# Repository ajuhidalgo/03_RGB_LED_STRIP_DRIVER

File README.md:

## Controlador de Tiras LED RGB con ESP32-C6-MINI

### Descripción
Este proyecto se centra en la creación de un controlador para tiras de LEDs RGB utilizando el microcontrolador **ESP32-C6-MINI**. El dispositivo está diseñado para ser compatible con **Google Home** y se conecta a través de **Wi-Fi**. El controlador permite seleccionar colores y efectos para las tiras LED.

### Componentes del Proyecto
1. **Circuito y PCB**: Diseñé el circuito y el PCB para el controlador utilizando **KiCad**. Puedes encontrar los esquemas y archivos Gerber en este repositorio.
2. **Carcasa**: Creé una carcasa en 3D para proteger el controlador con el programa **Fusion 360**. Los archivos STL y los detalles de impresión están disponibles en la carpeta de mecánica.
3. **Firmware**: El código fuente del firmware se encuentra en el repositorio. En la memoria del proyecto puedes obtener información acerca de la configuración.

### Características Clave
- **Microcontrolador**: Utilizamos el módulo **ESP32-C6-MINI** de Espressif Systems y transistores **mosfet** para controlar las tiras LED.
- **Interfaz de uso**: El dispositivo se controla a través del entorno **Google Home**. Permite la integración con la domótica del hogar, programar horarios de encendido o programar escenas. Esto lo conseguimos gracias al uso de la plataforma Sinric Pro.
- **Selección de Colores**: Los usuarios pueden elegir entre una amplia gama de colores para personalizar las tiras LED.

### Repositorio en GitHub
Puedes encontrar el código fuente, los esquemas, los archivos de Gerber, los archivos STL y más en este repositorio.

¡Buena suerte con tu proyecto! Si tienes alguna pregunta o necesitas más detalles, puedes ponerte en contacto conmigo.

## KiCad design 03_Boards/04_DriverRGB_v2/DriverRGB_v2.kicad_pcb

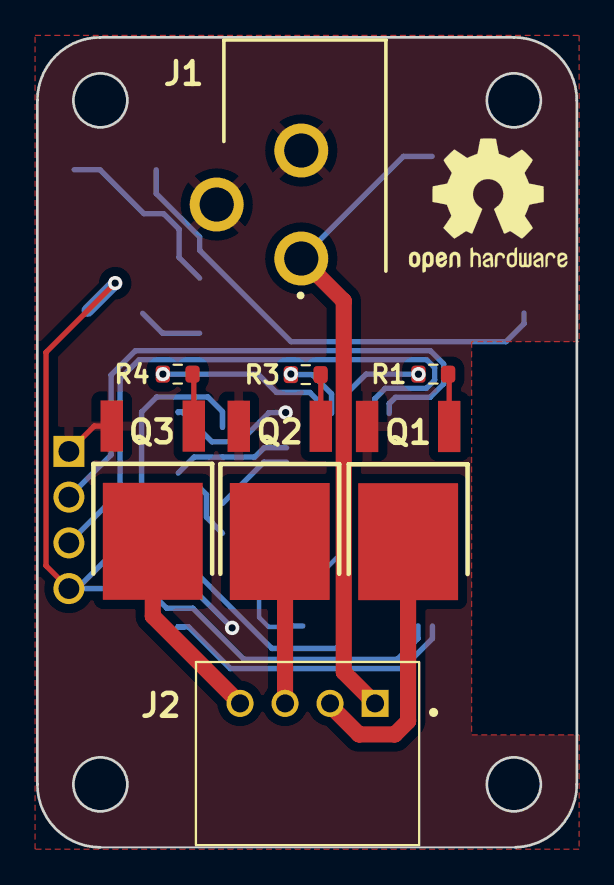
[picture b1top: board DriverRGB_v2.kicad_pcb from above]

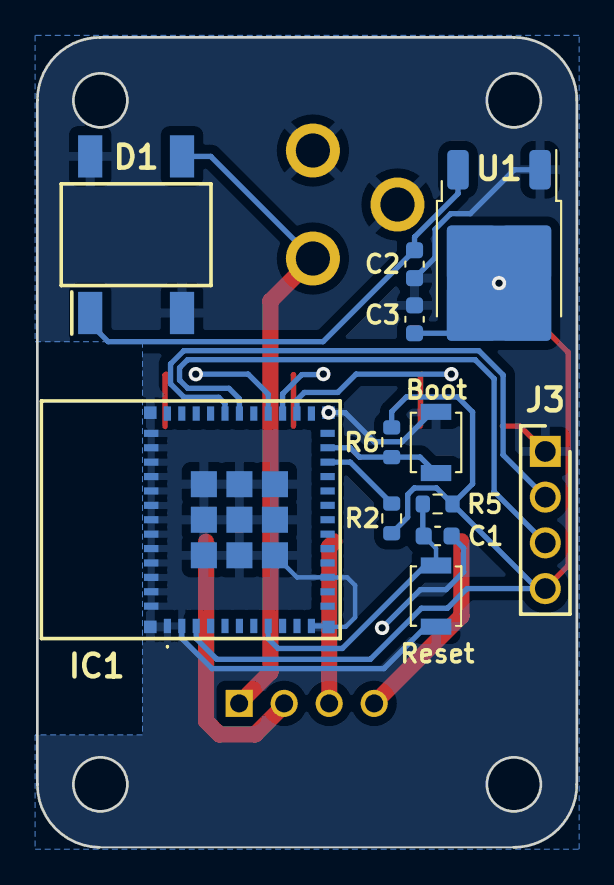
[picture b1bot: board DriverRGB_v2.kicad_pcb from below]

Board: 2 copper layers, 30.0 x 45.0 mm, 20 parts (12 on the bottom side), 18 nets.

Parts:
C1: 100nF; C_0603_1608Metric
C2, C3: 1uF; C_0603_1608Metric
D1: DF04S-E3; DF04S-E3_77
IC1: ESP32-C6-MINI-1-N4
J1: PJ-102A; PJ-102AH
J2: S4B-XH-A_LF__SN_
J3: 61300411121
Q1, Q2, Q3: FDD8880
R1, R2, R3, R4, R5, R6: 10kOhm; R_0603_1608Metric
S1: Reset; SW_SPST_B3U-1000P
S2: Boot; SW_SPST_B3U-1000P
U1: AMS1117CD-3.3; TO-252-2

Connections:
BLUE_OUT-: J2.4, Q3.3 (D)
EN: C1.1, IC1.8 (EN), R5.2, S1.2
GND: C1.2, C2.2, C3.2, D1.2 (-), D1.4, IC1.1 (GND_1), IC1.2 (GND_2), IC1.11 (GND_3), IC1.14 (GND_4), IC1.36 (GND_5), IC1.37 (GND_6), IC1.38 (GND_7), IC1.39 (GND_8), IC1.40 (GND_9), IC1.41 (GND_10), IC1.42 (GND_11), IC1.43 (GND_12), IC1.44 (GND_13), IC1.45 (GND_14), IC1.46 (GND_15), IC1.47 (GND_16), IC1.48 (GND_17), IC1.49 (GND_18), IC1.50 (GND_19), IC1.51 (GND_20), IC1.52 (GND_21), IC1.53 (GND_22), IC1.54 (GND_23), IC1.55 (GND_24), IC1.56 (GND_25), IC1.57 (GND_26), IC1.58 (GND_27), IC1.59 (GND_28), IC1.60 (GND_29), IC1.61 (GND_30), J1.2, J1.3, J3.1, Q1.2 (S), Q2.2 (S), Q3.2 (S), S1.1, S2.1, U1.1 (GND)
GREEN_OUT-: J2.3, Q2.3 (D)
IO9: IC1.23 (IO9), R6.2, S2.2
unnamed: C2.1, D1.1 (+), U1.3 (VI)
unnamed: IC1.22 (IO8), R2.2
unnamed: Q1.1 (G), R1.2
unnamed: Q2.1 (G), R3.2
unnamed: Q3.1 (G), R4.2
PWM_BLUE: IC1.26 (IO20), R4.1
PWM_GREEN: IC1.27 (IO21), R3.1
PWM_RED: IC1.28 (IO22), R1.1
PWR_IN: D1.3, J1.1, J2.1
RED_OUT-: J2.2, Q1.3 (D)
RX: IC1.30 (RXD0), J3.3
TX: IC1.31 (TXD0), J3.2
VDD: C3.1, IC1.3 (3V3), J3.4, R2.1, R5.1, R6.1, U1.2 (VO)

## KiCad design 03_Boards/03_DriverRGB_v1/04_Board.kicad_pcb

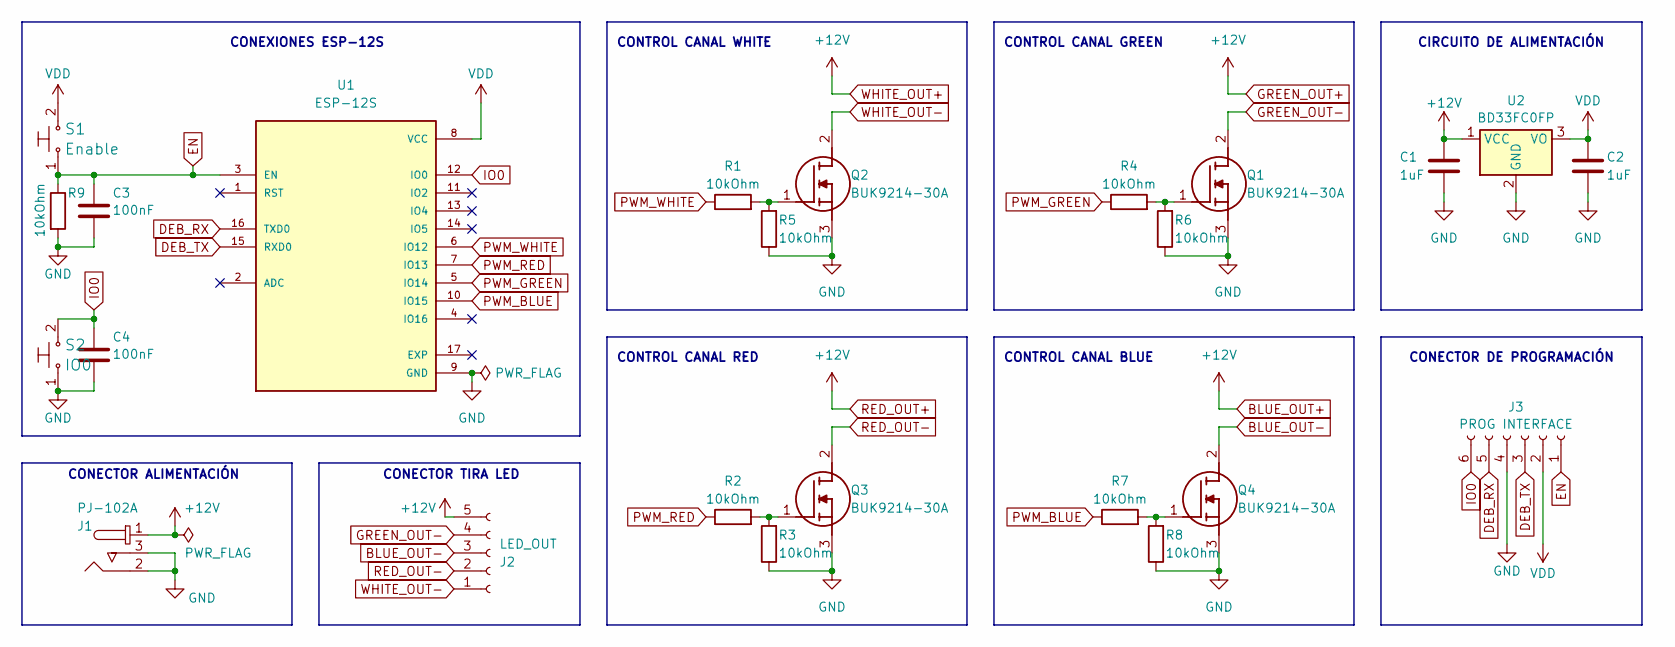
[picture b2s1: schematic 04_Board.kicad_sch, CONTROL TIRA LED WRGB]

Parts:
C1, C2: 1uF; C_1206_3216Metric
C3, C4: 100nF; C_1206_3216Metric
J1: PJ-102A; PJ-102AH; MPN PJ-102A; Digi-Key_PN CP-102A-ND
J2: LED_OUT; TerminalBlock_Phoenix_MKDS-1,5-5_1x05_P5.00mm_Horizontal
J3: PROG INTERFACE; PROG_INTERFACE
Q1, Q2, Q3, Q4: BUK9214-30A; BUK921430A118; Mouser Part Number 771-BUK9214-30A,118
R1, R2, R3, R4, R5, R6, R7, R8, R9: 10kOhm; R_1206_3216Metric
S1: Enable; SW_SPST_B3U-1000P; MPN B3U-1000P; Digi-Key_PN SW1020CT-ND
S2: IO0; SW_SPST_B3U-1000P; MPN B3U-1000P; Digi-Key_PN SW1020CT-ND
U1: ESP-12S; PARTREV V1.1
U2: BD33FC0FP; TO-252-2

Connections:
BLUE_OUT+: C1.1, J1.1, J2.5, U2.1 (VCC)
BLUE_OUT-: J2.3, Q4.2 (D)
DEB_RX: J3.5, U1.16 (TXD0)
DEB_TX: J3.3, U1.15 (RXD0)
EN: C3.1, J3.1, R9.1, S1.1, U1.3 (EN)
GND: C1.2, C2.2, C3.2, C4.2, J1.2, J1.3, J3.4, Q1.3 (S), Q2.3 (S), Q3.3 (S), Q4.3 (S), R3.1, R5.1, R6.1, R8.1, R9.2, S2.1, U1.9 (GND), U2.2 (GND)
GREEN_OUT-: J2.4, Q1.2 (D)
IO0: C4.1, J3.6, S2.2, U1.12 (IO0)
unnamed: Q1.1 (G), R4.2, R6.2
unnamed: Q2.1 (G), R1.2, R5.2
unnamed: Q3.1 (G), R2.2, R3.2
unnamed: Q4.1 (G), R7.2, R8.2
PWM_BLUE: R7.1, U1.10 (IO15)
PWM_GREEN: R4.1, U1.5 (IO14)
PWM_RED: R2.1, U1.7 (IO13)
PWM_WHITE: R1.1, U1.6 (IO12)
RED_OUT-: J2.2, Q3.2 (D)
VDD: C2.1, J3.2, S1.2, U1.8 (VCC), U2.3 (VO)
WHITE_OUT-: J2.1, Q2.2 (D)

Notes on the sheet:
CONECTOR DE PROGRAMACIÓN
CONTROL CANAL BLUE
CONEXIONES ESP-12S
CONECTOR ALIMENTACIÓN
CONTROL CANAL GREEN
CONTROL CANAL RED
CONECTOR TIRA LED
CIRCUITO DE ALIMENTACIÓN
CONTROL CANAL WHITE

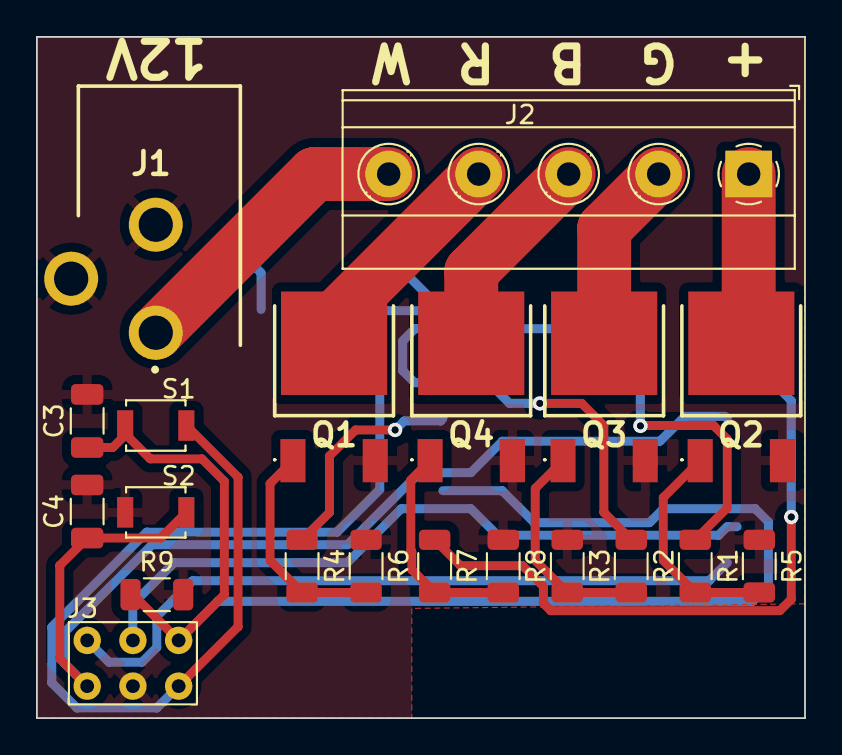
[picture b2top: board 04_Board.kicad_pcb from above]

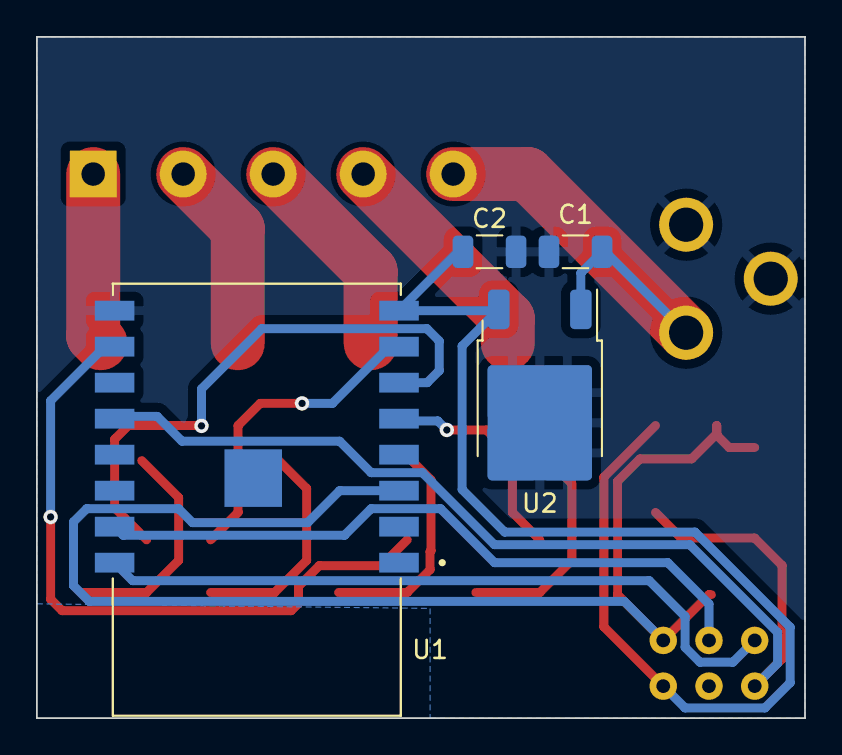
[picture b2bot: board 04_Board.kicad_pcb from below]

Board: 2 copper layers, 42.7 x 37.8 mm, 24 parts (4 on the bottom side), 19 nets.

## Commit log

2024-04-09 Libraries
2024-04-19 Docimentation
2024-04-23 Driver case
2024-05-01 Memoria
2024-06-18 Rediseño del esquemático del PCB
2024-06-20 Board desing v2
2024-07-02 Documentation
2024-07-02 Firmware update for esp32 support
2024-11-22 gerbers
